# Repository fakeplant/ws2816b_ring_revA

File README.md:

# WS2816B-2121 Ring
PCB experiment to test WS2816B-2121 LED chipsets.

### Software
[KiCad v7](https://www.kicad.org/)

### WS2816B-2121 Datasheet
[Downlaod PDF](https://datasheet.lcsc.com/lcsc/2012110135_Worldsemi-WS2816B-2121_C965560.pdf)

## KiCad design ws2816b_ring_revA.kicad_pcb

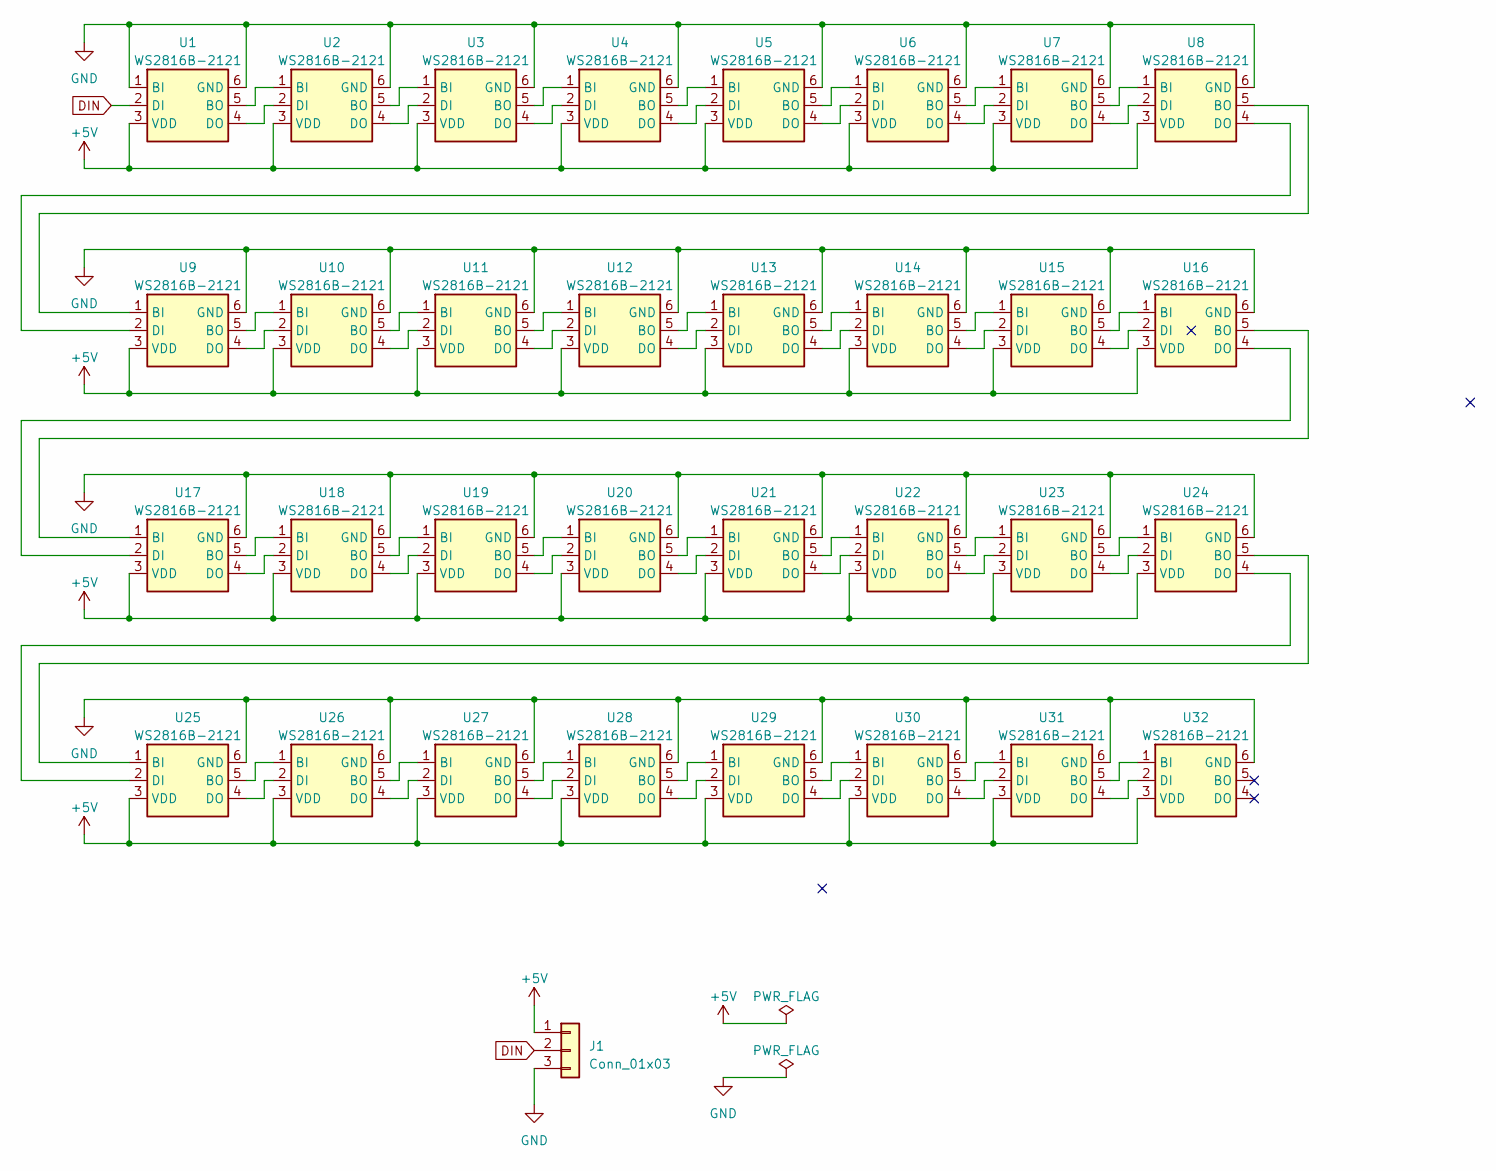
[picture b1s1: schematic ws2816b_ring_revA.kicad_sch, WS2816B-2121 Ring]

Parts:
J1: Conn_01x03; PinHeader_1x03_P1.00mm_Vertical
U1, U2, U3, U4, U5, U6, U7, U8, U9, U10, U11, U12, U13, U14, U15, U16, U17, U18, U19, U20, U21, U22, U23, U24, U25, U26, U27, U28, U29, U30, U31, U32: WS2816B-2121; LED_WS2816B-2121_2.1x2.1mm

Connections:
+5V: J1.1, U1.3 (VDD), U2.3 (VDD), U3.3 (VDD), U4.3 (VDD), U5.3 (VDD), U6.3 (VDD), U7.3 (VDD), U8.3 (VDD), U9.3 (VDD), U10.3 (VDD), U11.3 (VDD), U12.3 (VDD), U13.3 (VDD), U14.3 (VDD), U15.3 (VDD), U16.3 (VDD), U17.3 (VDD), U18.3 (VDD), U19.3 (VDD), U20.3 (VDD), U21.3 (VDD), U22.3 (VDD), U23.3 (VDD), U24.3 (VDD), U25.3 (VDD), U26.3 (VDD), U27.3 (VDD), U28.3 (VDD), U29.3 (VDD), U30.3 (VDD), U31.3 (VDD), U32.3 (VDD)
DIN: J1.2, U1.2 (DI)
GND: J1.3, U1.1 (BI), U1.6 (GND), U2.6 (GND), U3.6 (GND), U4.6 (GND), U5.6 (GND), U6.6 (GND), U7.6 (GND), U8.6 (GND), U9.6 (GND), U10.6 (GND), U11.6 (GND), U12.6 (GND), U13.6 (GND), U14.6 (GND), U15.6 (GND), U16.6 (GND), U17.6 (GND), U18.6 (GND), U19.6 (GND), U20.6 (GND), U21.6 (GND), U22.6 (GND), U23.6 (GND), U24.6 (GND), U25.6 (GND), U26.6 (GND), U27.6 (GND), U28.6 (GND), U29.6 (GND), U30.6 (GND), U31.6 (GND), U32.6 (GND)
unnamed: U1.5 (BO), U2.1 (BI)
unnamed: U1.4 (DO), U2.2 (DI)
unnamed: U2.5 (BO), U3.1 (BI)
unnamed: U2.4 (DO), U3.2 (DI)
unnamed: U3.5 (BO), U4.1 (BI)
unnamed: U3.4 (DO), U4.2 (DI)
unnamed: U4.5 (BO), U5.1 (BI)
unnamed: U4.4 (DO), U5.2 (DI)
unnamed: U5.5 (BO), U6.1 (BI)
unnamed: U5.4 (DO), U6.2 (DI)
unnamed: U6.5 (BO), U7.1 (BI)
unnamed: U6.4 (DO), U7.2 (DI)
unnamed: U7.5 (BO), U8.1 (BI)
unnamed: U7.4 (DO), U8.2 (DI)
unnamed: U8.5 (BO), U9.1 (BI)
unnamed: U8.4 (DO), U9.2 (DI)
unnamed: U9.5 (BO), U10.1 (BI)
unnamed: U10.5 (BO), U11.1 (BI)
unnamed: U9.4 (DO), U10.2 (DI)
unnamed: U10.4 (DO), U11.2 (DI)
unnamed: U11.5 (BO), U12.1 (BI)
unnamed: U11.4 (DO), U12.2 (DI)
unnamed: U12.5 (BO), U13.1 (BI)
unnamed: U12.4 (DO), U13.2 (DI)
unnamed: U13.5 (BO), U14.1 (BI)
unnamed: U13.4 (DO), U14.2 (DI)
unnamed: U14.5 (BO), U15.1 (BI)
unnamed: U14.4 (DO), U15.2 (DI)
unnamed: U15.5 (BO), U16.1 (BI)
unnamed: U15.4 (DO), U16.2 (DI)
unnamed: U16.5 (BO), U17.1 (BI)
unnamed: U16.4 (DO), U17.2 (DI)
unnamed: U17.5 (BO), U18.1 (BI)
unnamed: U17.4 (DO), U18.2 (DI)
unnamed: U18.5 (BO), U19.1 (BI)
unnamed: U18.4 (DO), U19.2 (DI)
unnamed: U19.5 (BO), U20.1 (BI)
unnamed: U19.4 (DO), U20.2 (DI)
unnamed: U20.5 (BO), U21.1 (BI)
unnamed: U20.4 (DO), U21.2 (DI)
unnamed: U21.5 (BO), U22.1 (BI)
unnamed: U21.4 (DO), U22.2 (DI)
unnamed: U22.5 (BO), U23.1 (BI)
unnamed: U22.4 (DO), U23.2 (DI)
unnamed: U23.5 (BO), U24.1 (BI)
unnamed: U23.4 (DO), U24.2 (DI)
unnamed: U24.5 (BO), U25.1 (BI)
unnamed: U24.4 (DO), U25.2 (DI)
unnamed: U25.5 (BO), U26.1 (BI)
unnamed: U25.4 (DO), U26.2 (DI)
unnamed: U26.5 (BO), U27.1 (BI)
unnamed: U26.4 (DO), U27.2 (DI)
unnamed: U27.5 (BO), U28.1 (BI)
unnamed: U27.4 (DO), U28.2 (DI)
unnamed: U28.5 (BO), U29.1 (BI)
unnamed: U28.4 (DO), U29.2 (DI)
unnamed: U29.5 (BO), U30.1 (BI)
unnamed: U29.4 (DO), U30.2 (DI)
unnamed: U30.5 (BO), U31.1 (BI)
unnamed: U30.4 (DO), U31.2 (DI)
unnamed: U31.5 (BO), U32.1 (BI)
unnamed: U31.4 (DO), U32.2 (DI)

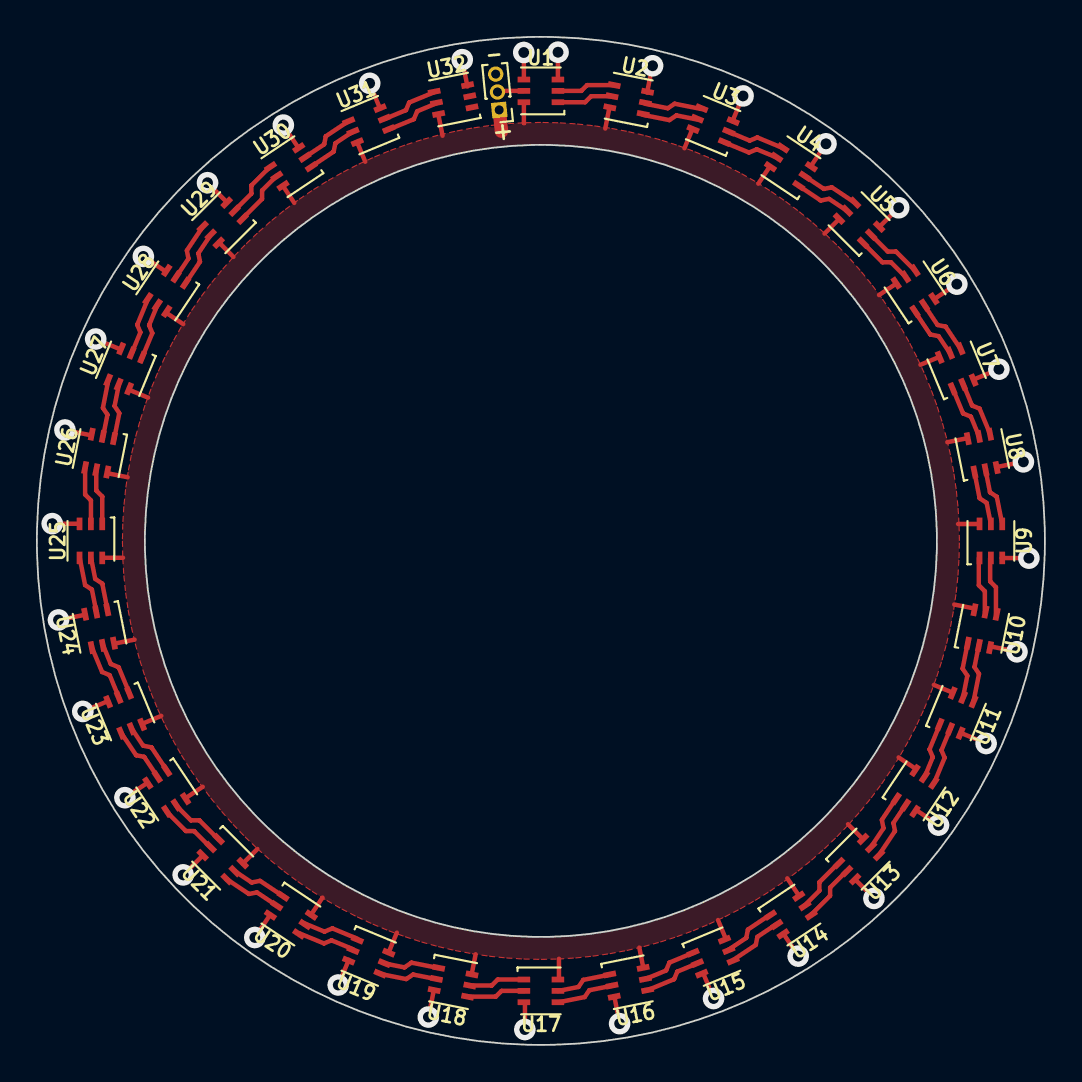
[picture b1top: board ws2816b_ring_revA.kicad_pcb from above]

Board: 2 copper layers, 56.0 x 56.0 mm, 33 parts (0 on the bottom side), 65 nets.

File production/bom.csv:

Designator,Footprint,Quantity,Value,LCSC Part #
"U1, U10, U11, U12, U13, U14, U15, U16, U17, U18, U19, U2, U20, U21, U22, U23, U24, U25, U26, U27, U28, U29, U3, U30, U31, U32, U4, U5, U6, U7, U8, U9",LED_WS2816B-2121_2.1x2.1mm,32,WS2816B-2121,C965561

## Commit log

2023-12-20 revA
